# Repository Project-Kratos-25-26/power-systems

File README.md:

# power-systems
PCB files used in the rover

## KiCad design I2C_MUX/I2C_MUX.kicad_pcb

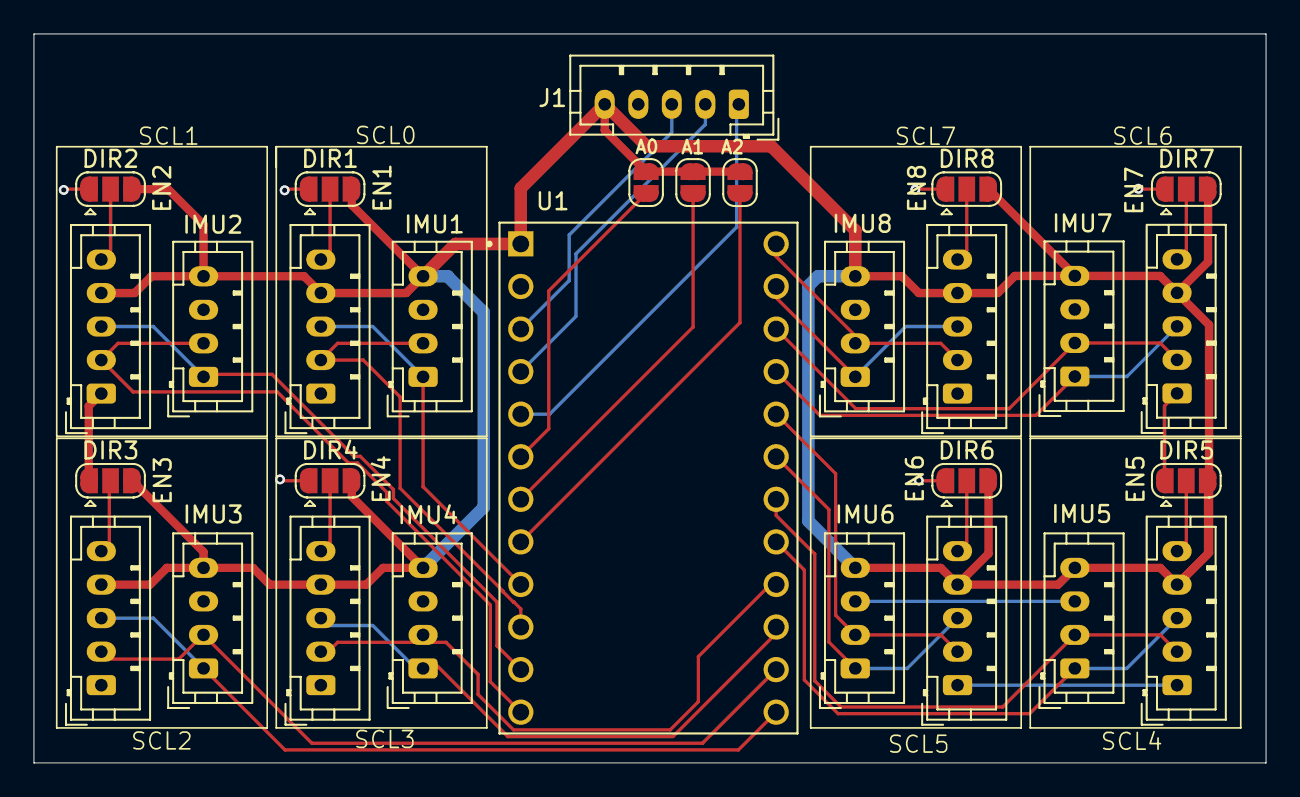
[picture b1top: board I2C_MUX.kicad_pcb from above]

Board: 2 copper layers, 73.5 x 43.5 mm, 29 parts (0 on the bottom side), 32 nets.

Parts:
A0, A1, A2: SolderJumper_2_Open; SolderJumper-2_P1.3mm_Open_RoundedPad1.0x1.5mm
DIR1, DIR2, DIR3, DIR4, DIR5, DIR6, DIR7, DIR8: SolderJumper_3_Open; SolderJumper-3_P1.3mm_Open_RoundedPad1.0x1.5mm
EN1, EN2, EN3, EN4, EN5, EN6, EN7, EN8: Conn_01x05_Pin; JST_PH_B5B-PH-K_1x05_P2.00mm_Vertical
IMU1, IMU2, IMU3, IMU4, IMU5, IMU6, IMU7, IMU8: Conn_01x04_Pin; JST_PH_B4B-PH-K_1x04_P2.00mm_Vertical
J1: Conn_01x05; JST_PH_B5B-PH-K_1x05_P2.00mm_Vertical
U1: 2717; MODULE_2717

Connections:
/DIR1: DIR1.2 (C), EN1.5
/DIR2: DIR2.2 (C), EN2.5
/DIR3: DIR3.2 (C), EN3.5
/DIR4: DIR4.2 (C), EN4.5
/DIR5: DIR5.2 (C), EN5.5
/DIR6: DIR6.2 (C), EN6.5
/DIR7: DIR7.2 (C), EN7.5
/DIR8: DIR8.2 (C), EN8.5
/RST: J1.1, U1.5 (RST)
/SCL: J1.2, U1.4 (SCL)
/SCL0: EN1.2, IMU1.2, U1.10 (SCL0)
/SCL1: EN2.2, IMU2.2, U1.12 (SCL1)
/SCL2: EN3.2, IMU3.2, U1.14 (SCL2)
/SCL3: EN4.2, IMU4.2, U1.16 (SCL3)
/SCL4: EN5.2, IMU5.2, U1.18 (SCL4)
/SCL5: EN6.2, IMU6.2, U1.20 (SCL5)
/SCL6: EN7.2, IMU7.2, U1.22 (SCL6)
/SCL7: EN8.2, IMU8.2, U1.24 (SCL7)
/SDA: J1.3, U1.3 (SDA)
/SDA0: EN1.3, IMU1.1, U1.9 (SDA0)
/SDA1: EN2.3, IMU2.1, U1.11 (SDA1)
/SDA2: EN3.3, IMU3.1, U1.13 (SDA2)
/SDA3: EN4.3, IMU4.1, U1.15 (SDA3)
/SDA4: EN5.3, IMU5.1, U1.17 (SDA4)
/SDA5: EN6.3, IMU6.1, U1.19 (SDA5)
/SDA6: EN7.3, IMU7.1, U1.21 (SDA6)
/SDA7: EN8.3, IMU8.1, U1.23 (SDA7)
GND: DIR1.1 (A), DIR2.1 (A), DIR3.1 (A), DIR4.1 (A), DIR5.1 (A), DIR6.1 (A), DIR7.1 (A), DIR8.1 (A), EN1.1, EN2.1, EN3.1, EN4.1, EN5.1, EN6.1, EN7.1, EN8.1, IMU1.3, IMU2.3, IMU3.3, IMU4.3, IMU5.3, IMU6.3, IMU7.3, IMU8.3, J1.4, U1.2 (GND)
unnamed: A0.2 (B), U1.6 (A0)
unnamed: A1.2 (B), U1.7 (A1)
unnamed: A2.2 (B), U1.8 (A2)
VCC: A0.1 (A), A1.1 (A), A2.1 (A), DIR1.3 (B), DIR2.3 (B), DIR3.3 (B), DIR4.3 (B), DIR5.3 (B), DIR6.3 (B), DIR7.3 (B), DIR8.3 (B), EN1.4, EN2.4, EN3.4, EN4.4, EN5.4, EN6.4, EN7.4, EN8.4, IMU1.4, IMU2.4, IMU3.4, IMU4.4, IMU5.4, IMU6.4, IMU7.4, IMU8.4, J1.5, U1.1 (VIN)
